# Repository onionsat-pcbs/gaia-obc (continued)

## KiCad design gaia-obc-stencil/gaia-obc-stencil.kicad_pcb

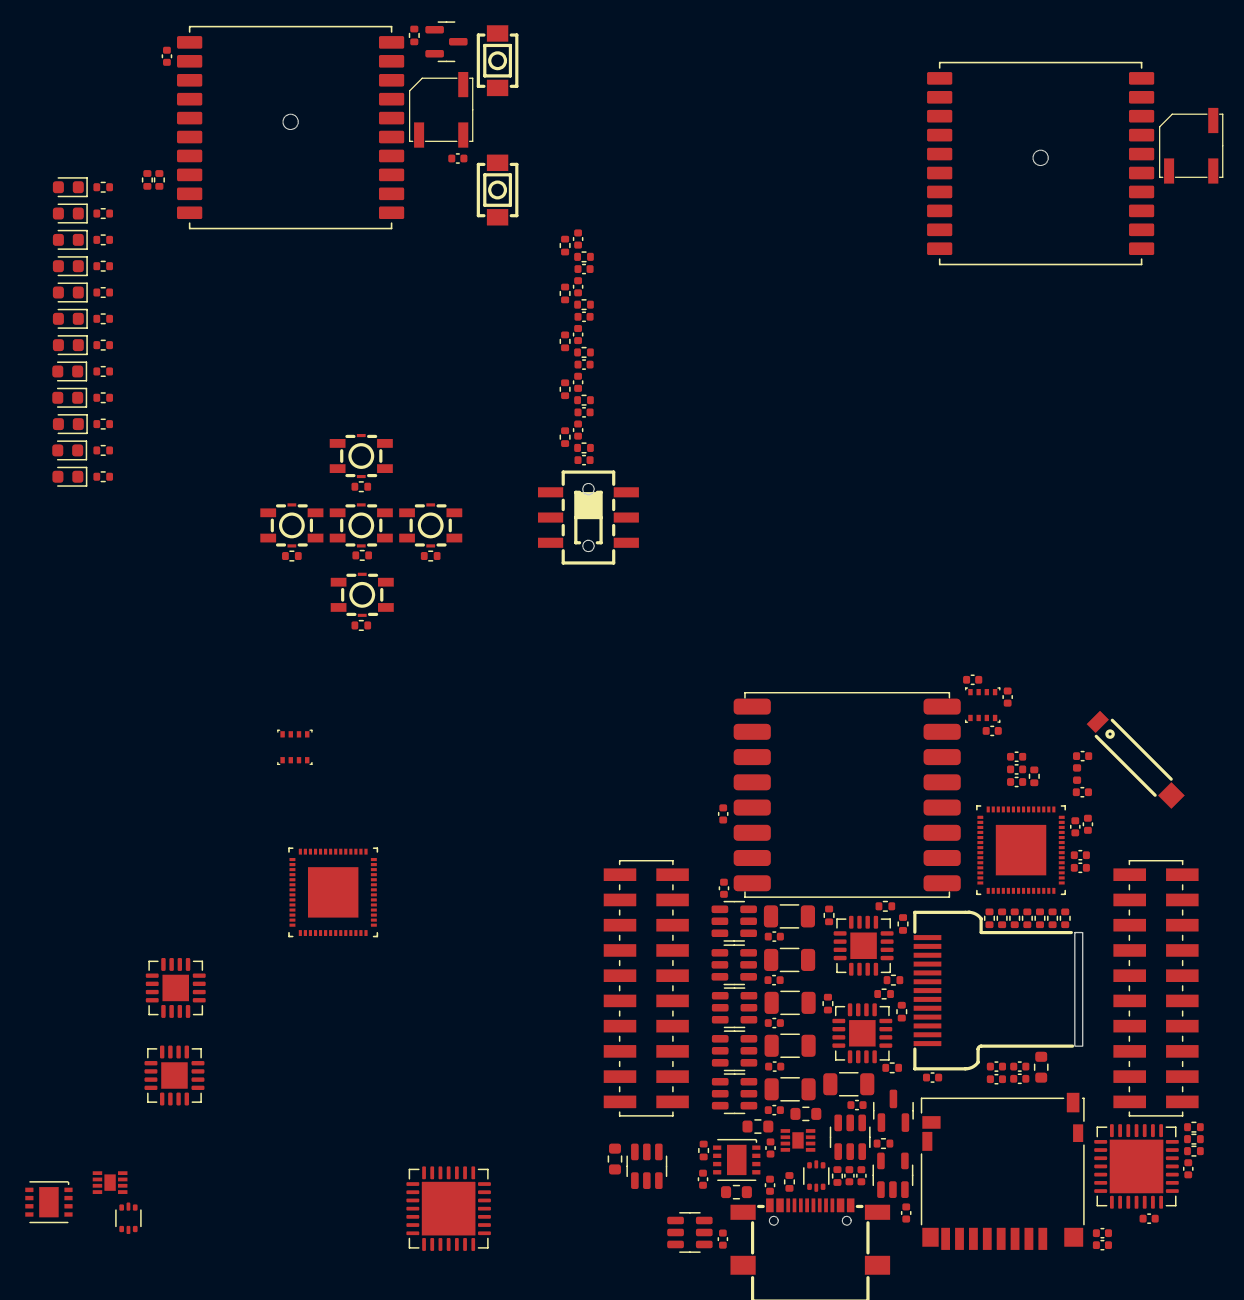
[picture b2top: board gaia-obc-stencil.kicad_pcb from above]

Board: 2 copper layers, 171 parts (1 on the bottom side), 121 nets, no tracks yet.

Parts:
AE1: Antenna; ANT-SMD_L8.0-W1.0
BZ1, BZ1#2: Buzzer; buzzer_MLT-5020
C1, C2, C3, C5, C8, C9, C10, C11, C12, C25, C32, C36, C39, C40, C41, C43, C44, C45, C48: 100nF; C_0402_1005Metric
C4, C33, C35, C37: 10uF; C_0402_1005Metric
C6, C7, C13, C14, C15, C16, C17, C18, C24, C26, C27, C28, C29, C30, C31, C34, C38, C42: 1uF; C_0402_1005Metric
C19, C20, C21, C22, C23: 1nF; C_0402_1005Metric
C46: 2,4pF; C_0402_1005Metric
C47: 2,0pF; C_0402_1005Metric
D1, D2, D3, D4, D5, D6, D7, D8, D9, D10, D11, D12: LED_Small; LED_0603_1608Metric
IC1, IC1#2: MAX17048G+T10; SON50P200X200X80-9N-D
J1: USB_C_Receptacle_USB2.0_16P; USB-SMD_TYPE-C-16PQT-073
J2, J3: Conn_02x10_Odd_Even; PinHeader_2x10_P2.00mm_Vertical_SMD
J5: Micro_SD_Card_Det2; microSD_HC_Hirose_DM3D-SF
L1: 2,4nH; L_0402_1005Metric
Q1: IRLML6244; SOT-23
Q2: FS8205A; SOT-23-6
Q3: BSS138; SOT-23
R1, R2, R3, R13, R14, R15, R16, R17, R18, R20, R23, R24, R25, R26, R27, R28, R29, R30, R31, R59, R61, R62, R63, R64, R65: 10k; R_0402_1005Metric
R4, R5: 5.1k; R_0402_1005Metric
R6, R7, R8, R9, R10, R11, R12, R21, R22, R49, R50: TBA; R_0402_1005Metric
R19, R53: 1k; R_0402_1005Metric
R32, R33, R34, R35, R36, R37: 0,1; R_1206_3216Metric
R38, R39, R40, R41, R42, R43, R44, R45, R46, R47: 0; R_0402_1005Metric
R48: 100; R_0603_1608Metric
R51: 1k; R_0603_1608Metric
R54, R55: 100k; R_0603_1608Metric
R56, R57: 470; R_0402_1005Metric
R58: R_Small; R_0402_1005Metric
R60: 10; R_0603_1608Metric
SW1, SW2: SW_Push; KEY-SMD_L4.0-W3.0-LS4.9-1
SW3, SW4, SW5, SW6, SW7: SW_Push; KEY-SMD_4P-L3.1-W3.1-P2.00-LS4.0
SW8: SW_Slide_DPDT; MS-22D28-G020
U1, U1#2: MCP23017_ML; QFN-28-1EP_6x6mm_P0.65mm_EP4.25x4.25mm
U2, U2#2: USBLC6-2P6; SOT-666
U3, U3#2: ESP32-S3-PICO-1-N8R2; PQFN40P700X700X106-57N
U4, U4#2, U5, U5#2: INA3221; Texas_RGV0016A_VQFN-16-1EP_4x4mm_P0.65mm_EP2.1x2.1mm
U6, U7, U8, U9, U10: TPS22917DBV; SOT-23-6
U11: AP2112K-3.3; SOT-23-6
U12: DW01A; SOT-23-6
U13: AP2112K-3.0; SOT-23-5
U14, U14#2: LGS4056HDB; DFN-8-1EP_3x3mm_P0.65mm_EP1.55x2.4mm
U15, U15#2: CD-PA1616; XCVR_CD-PA1616D
U16: RFM95W-868S2; HOPERF_RFM9XW_SMD
U17, U17#2: BME280; Bosch_LGA-8_2.5x2.5mm_P0.65mm_ClockwisePinNumbering
U18: OLED-SMD_ST7735S

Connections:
+3.3V: BZ1.1 (+), BZ1#2.1 (+), C1.2, C2.1, C7.1, C8.1, C9.1, C10.1, C11.1, C12.1, C13.1, C25.1, C26.2, C39.1, C40.2, C41.2, C42.2, C43.1, C44.1, C45.2, C48.2, J5.4 (VDD), R1.1, R2.1, R3.1, R13.1, R14.2, R15.2, R16.2, R17.2, R18.2, R20.2, R23.2, R24.1, R25.1, R26.1, R27.1, R28.1, R29.1, SW3.2, SW4.2, SW5.2, SW6.2, SW7.2, U1.5 (VDD), U1#2.5 (VDD), U3.2 (VDD3P3), U3.3 (VDD3P3), U3.20 (VDD3P3_RTC), U3.46 (VDD3P3_CPU), U3.55 (VDDA), U3.56 (VDDA), U3#2.2 (VDD3P3), U3#2.3 (VDD3P3), U3#2.20 (VDD3P3_RTC), U3#2.46 (VDD3P3_CPU), U3#2.55 (VDDA), U3#2.56 (VDDA), U4.4 (VS), U4#2.4 (VS), U5.4 (VS), U5.5 (A0), U5#2.4 (VS), U5#2.5 (A0), U11.5 (VOUT), U15.1 (VCC), U15#2.1 (VCC), U16.13 (3.3V), U17.2 (CSB), U17.6 (VDDIO), U17.8 (VDD), U17#2.2 (CSB), U17#2.6 (VDDIO), U17#2.8 (VDD)
+3V0: C36.1, C38.2, R59.1, U13.5 (VOUT), U18.10 (VCC), U18.12 (LEDA)
+BATT: C33.2, C37.2, IC1.2 (CELL), IC1.3 (VDD), IC1#2.2 (CELL), IC1#2.3 (VDD), J3.17, J3.18, R48.1, R55.2, SW8.1 (A), SW8.6 (C), U14.5 (BAT), U14#2.5 (BAT)
-BATT: J3.19, J3.20, Q2.3, R51.1
/EN_A1: U1.17 (GPA0), U1#2.17 (GPA0), U6.3 (ON)
/EN_A2: U1.18 (GPA1), U1#2.18 (GPA1), U7.3 (ON)
/EN_A3: U1.19 (GPA2), U1#2.19 (GPA2), U8.3 (ON)
/EN_B1: U1.20 (GPA3), U1#2.20 (GPA3), U9.3 (ON)
/EN_B2: U1.21 (GPA4), U1#2.21 (GPA4), U10.3 (ON)
/EXP0_USART_RXD: J2.14, U3.41 (GPIO36), U3#2.41 (GPIO36)
/EXP0_USART_TXD: J2.12, U3.42 (GPIO37), U3#2.42 (GPIO37)
/EXP1_SPI_CS: J2.5, U3.43 (GPIO38), U3#2.43 (GPIO38)
/EXP2_USART_RXD: J2.13, U3.39 (GPIO34), U3#2.39 (GPIO34)
/EXP2_USART_TXD: J2.11, U3.40 (GPIO35), U3#2.40 (GPIO35)
/GPS_RX: R57.2, U3.6 (GPIO1), U3#2.6 (GPIO1)
/GPS_TX: R56.1, U3.7 (GPIO2), U3#2.7 (GPIO2)
/LORA_CS: U3.27 (GPIO21), U3#2.27 (GPIO21), U16.5 (NSS)
/LORA_RESET: U3.38 (GPIO33), U3#2.38 (GPIO33), U16.6 (RESET)
/PB1: R61.2, SW3.1, U1.25 (GPB0), U1#2.25 (GPB0)
/PB2: R62.2, SW4.1, U1.26 (GPB1), U1#2.26 (GPB1)
/PB3: R63.2, SW5.1, U1.27 (GPB2), U1#2.27 (GPB2)
/PB4: R64.2, SW6.1, U1.28 (GPB3), U1#2.28 (GPB3)
/PB5: R65.2, SW7.1, U1.1 (GPB4), U1#2.1 (GPB4)
/Power Supply Unit/OBC_BATT: C24.1, C34.1, R37.2, U5.2 (IN+3), U5#2.2 (IN+3), U11.1 (VIN), U11.3 (EN), U13.1 (VIN), U13.3 (EN)
/SCREEN_CLK: U3.11 (GPIO6), U3#2.11 (GPIO6), U18.4 (SCL)
/SCREEN_CS: U3.8 (GPIO3), U3#2.8 (GPIO3), U18.7 (CS)
/SCREEN_DC: U3.10 (GPIO5), U3#2.10 (GPIO5), U18.5 (RS)
/SCREEN_MOSI: U3.12 (GPIO7), U3#2.12 (GPIO7), U18.3 (SDA)
/SCREEN_RESET: U3.9 (GPIO4), U3#2.9 (GPIO4), U18.6 (RES)
/SD_CS: J5.2 (DAT3/CD), U3.23 (GPIO17), U3#2.23 (GPIO17)
/USB_D+: U2.4 (I/O2), U2#2.4 (I/O2), U3.26 (GPIO20), U3#2.26 (GPIO20)
/USB_D-: U2.6 (I/O1), U2#2.6 (I/O1), U3.25 (GPIO19), U3#2.25 (GPIO19)
/VOUT_A1: C27.2, J3.1, J3.2, R38.2, R43.2, U6.6 (VOUT)
/VOUT_A2: C28.2, J3.3, J3.4, R39.2, R44.2, U7.6 (VOUT)
/VOUT_A3: C29.2, J3.5, J3.6, R40.2, R45.2, U8.6 (VOUT)
/VOUT_B1: C30.2, J3.7, J3.8, R41.2, R46.2, U9.6 (VOUT)
/VOUT_B2: C31.2, J3.9, J3.10, R42.2, R47.2, U10.6 (VOUT)
GND: C1.1, C2.2, C3.2, C4.1, C5.1, C6.2, C7.2, C8.2, C9.2, C10.2, C11.2, C12.2, C13.2, C14.1, C15.1, C16.1, C17.1, C18.1, C24.2, C25.2, C26.1, C27.1, C28.1, C29.1, C30.1, C31.1, C32.2, C33.1, C34.2, C35.1, C36.2, C37.1, C38.1, C39.2, C40.1, C41.1, C42.1, C43.2, C44.2, C45.1, C46.2, C47.1, C48.1, IC1.1 (CTG), IC1.4 (GND), IC1.9 (EP), IC1#2.1 (CTG), IC1#2.4 (GND), IC1#2.9 (EP), J1.A1B12 (GND), J1.B1A12 (GND), J1.S1 (SHIELD), J2.7, J2.9, J2.17, J2.18, J2.19, J2.20, J3.13, J3.14, J3.15, J3.16, J5.6 (VSS), J5.11 (SHIELD), Q1.2 (S), Q2.1, Q3.2 (S), R4.1, R5.2, R6.2, R7.2, R8.2, R9.2, R10.2, R11.2, R12.2, R21.2, R22.2, R43.1, R44.1, R45.1, R46.1, R47.1, R53.2, R54.1, R58.2, R61.1, R62.1, R63.1, R64.1, R65.1, SW1.1, SW2.1, U1.6 (VSS), U1.11 (A0), U1.12 (A1), U1.13 (A2), U1.29 (EP), U1#2.6 (VSS), U1#2.11 (A0), U1#2.12 (A1), U1#2.13 (A2), U1#2.29 (EP), U2.2 (GND), U2#2.2 (GND), U3.57 (GND), U3#2.57 (GND), U4.3 (GND), U4.5 (A0), U4.17 (EP), U4#2.3 (GND), U4#2.5 (A0), U4#2.17 (EP), U5.3 (GND), U5.17 (EP), U5#2.3 (GND), U5#2.17 (EP), U6.2 (GND), U7.2 (GND), U8.2 (GND), U9.2 (GND), U10.2 (GND), U11.2 (GND), U12.6 (GND), U13.2 (GND), U14.1 (TEMP), U14.3 (GND), U14.9 (EPAD), U14#2.1 (TEMP), U14#2.3 (GND), U14#2.9 (EPAD), U15.3 (GND), U15.8 (GND), U15.12 (GND), U15.19 (GND), U15#2.3 (GND), U15#2.8 (GND), U15#2.12 (GND), U15#2.19 (GND), U16.1 (GND), U16.8 (GND), U16.10 (GND), U17.1 (GND), U17.5 (SDO), U17.7 (GND), U17#2.1 (GND), U17#2.5 (SDO), U17#2.7 (GND), U18.8 (GND), U18.13 (GND)
I2C_1_SCL: IC1.7 (SCL), IC1#2.7 (SCL), J2.4, R15.1, U1.8 (SCK), U1#2.8 (SCK), U3.14 (GPIO9), U3#2.14 (GPIO9), U4.6 (SCL), U4#2.6 (SCL), U5.6 (SCL), U5#2.6 (SCL), U17.4 (SCK), U17#2.4 (SCK)
I2C_1_SDA: IC1.8 (SDA), IC1#2.8 (SDA), J2.2, R14.1, U1.9 (SDA), U1#2.9 (SDA), U3.13 (GPIO8), U3#2.13 (GPIO8), U4.7 (SDA), U4#2.7 (SDA), U5.7 (SDA), U5#2.7 (SDA), U17.3 (SDI), U17#2.3 (SDI)
I2C_2_SCL: J2.3, R20.1, U3.16 (GPIO11), U3#2.16 (GPIO11)
I2C_2_SDA: J2.1, R17.1, U3.15 (GPIO10), U3#2.15 (GPIO10)
unnamed: AE1.1 (A), C46.1, L1.1
unnamed: BZ1.2 (-), BZ1#2.2 (-), Q1.3 (D)
unnamed: D1.1 (K), R6.1
unnamed: D2.2 (A), U1.2 (GPB5), U1#2.2 (GPB5)
unnamed: D2.1 (K), R7.1
unnamed: D3.2 (A), U1.4 (GPB7), U1#2.4 (GPB7)
unnamed: D3.1 (K), R8.1
unnamed: D4.2 (A), U1.3 (GPB6), U1#2.3 (GPB6)
unnamed: D4.1 (K), R9.1
unnamed: D5.2 (A), U1.24 (GPA7), U1#2.24 (GPA7)
unnamed: D5.1 (K), R10.1
unnamed: D6.2 (A), U1.23 (GPA6), U1#2.23 (GPA6)
unnamed: D6.1 (K), R11.1
unnamed: D7.2 (A), U1.22 (GPA5), U1#2.22 (GPA5)
unnamed: D7.1 (K), R12.1
unnamed: D8.2 (A), U3.51 (GPIO45), U3#2.51 (GPIO45)
unnamed: D8.1 (K), R21.1
unnamed: D9.2 (A), U3.52 (GPIO46), U3#2.52 (GPIO46)
unnamed: D9.1 (K), R22.1
unnamed: D10.2 (A), U14.7 (~CHRG), U14#2.7 (~CHRG)
unnamed: D10.1 (K), R49.1
unnamed: D11.2 (A), U14.6 (~STDBY), U14#2.6 (~STDBY)
unnamed: D11.1 (K), R50.2
unnamed: D12.2 (A), U15.5 (3D-FIX), U15#2.5 (3D-FIX)
unnamed: D12.1 (K), R58.1
unnamed: IC1.6 (QSTRT), IC1#2.6 (QSTRT), R54.2
unnamed: IC1.5 (~ALRT), IC1#2.5 (~ALRT), R55.1
unnamed: J1.A5 (CC1), R4.2
unnamed: J1.B5 (CC2), R5.1
unnamed: J1.A6 (D+), J1.B6 (D+), U2.3 (I/O2), U2#2.3 (I/O2)
unnamed: J1.A7 (D-), J1.B7 (D-), U2.1 (I/O1), U2#2.1 (I/O1)
unnamed: Q1.1 (G), R19.2
unnamed: Q3.3 (D), R60.1
unnamed: Q3.1 (G), R59.2
unnamed: R2.2, U1.16 (INTA), U1#2.16 (INTA)
unnamed: R1.2, U1.15 (INTB), U1#2.15 (INTB)
unnamed: R3.2, U1.14 (~RESET), U1#2.14 (~RESET)
unnamed: C5.2, C6.1, R13.2, SW1.2, U3.4 (CHIP_PU), U3#2.4 (CHIP_PU)
unnamed: SW2.2, U3.5 (GPIO0), U3#2.5 (GPIO0)
unnamed: R19.1, U3.24 (GPIO18), U3#2.24 (GPIO18)
unnamed: C47.2, L1.2, U3.1 (LNA_IN), U3#2.1 (LNA_IN)
unnamed: R28.2, U4.9 (CRITICAL), U4#2.9 (CRITICAL)
unnamed: C14.2, C19.1, R32.2, U4.12 (IN+1), U4#2.12 (IN+1), U6.1 (VIN)
unnamed: C15.2, C20.1, R33.2, U4.15 (IN+2), U4#2.15 (IN+2), U7.1 (VIN)
unnamed: C16.2, C21.1, R34.2, U4.2 (IN+3), U4#2.2 (IN+3), U8.1 (VIN)
unnamed: R30.2, U4.10 (PV), U4#2.10 (PV)
unnamed: R24.2, U4.13 (TC), U4#2.13 (TC)
unnamed: R30.1, U4.16 (VPU), U4#2.16 (VPU)
unnamed: R26.2, U4.8 (WARNING), U4#2.8 (WARNING)
unnamed: R29.2, U5.9 (CRITICAL), U5#2.9 (CRITICAL)
unnamed: C17.2, C22.1, R35.2, U5.12 (IN+1), U5#2.12 (IN+1), U9.1 (VIN)
unnamed: R31.2, U5.10 (PV), U5#2.10 (PV)
unnamed: R25.2, U5.13 (TC), U5#2.13 (TC)
unnamed: R31.1, U5.16 (VPU), U5#2.16 (VPU)
unnamed: R27.2, U5.8 (WARNING), U5#2.8 (WARNING)
unnamed: C19.2, U6.4 (CT)
unnamed: R38.1, U6.5 (QOD)
unnamed: C20.2, U7.4 (CT)
unnamed: R39.1, U7.5 (QOD)
unnamed: C21.2, U8.4 (CT)
unnamed: R40.1, U8.5 (QOD)
unnamed: C22.2, U9.4 (CT)
unnamed: R41.1, U9.5 (QOD)
unnamed: C23.2, U10.4 (CT)
unnamed: R42.1, U10.5 (QOD)
unnamed: C18.2, C23.1, R36.2, U5.15 (IN+2), U5#2.15 (IN+2), U10.1 (VIN)
unnamed: R51.2, U12.2 (CS)
unnamed: Q2.4, U12.3 (OC)
unnamed: Q2.6, U12.1 (OD)
unnamed: C32.1, R48.2, U12.5 (VCC)
unnamed: R53.1, U14.2 (PROG), U14#2.2 (PROG)
unnamed: R57.1, U15.10 (RX), U15#2.10 (RX)
unnamed: R56.2, U15.9 (TX), U15#2.9 (TX)
unnamed: R60.2, U18.11 (LEDK)
SPI_0_MISO: J2.6, J5.7 (DAT0), R16.1, U3.17 (GPIO12), U3#2.17 (GPIO12), U16.2 (MISO)
SPI_0_MOSI: J2.8, J5.3 (CMD), R18.1, U3.18 (GPIO13), U3#2.18 (GPIO13), U16.3 (MOSI)
SPI_0_SCLK: J2.10, J5.5 (CLK), R23.1, U3.19 (GPIO14), U3#2.19 (GPIO14), U16.4 (SCK)
VBUS: C3.1, C4.2, C35.2, D1.2 (A), J1.A4B9 (VBUS), J1.B4A9 (VBUS), R49.2, R50.1, U2.5 (VBUS), U2#2.5 (VBUS), U14.4 (V_{CC}), U14.8 (CE), U14#2.4 (V_{CC}), U14#2.8 (CE)
VCC: R32.1, R33.1, R34.1, R35.1, R36.1, R37.1, SW8.2 (B), SW8.5 (B), U4.1 (IN-3), U4.11 (IN-1), U4.14 (IN-2), U4#2.1 (IN-3), U4#2.11 (IN-1), U4#2.14 (IN-2), U5.1 (IN-3), U5.11 (IN-1), U5.14 (IN-2), U5#2.1 (IN-3), U5#2.11 (IN-1), U5#2.14 (IN-2)

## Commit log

2025-05-28 initial release
2025-06-02 creating different sheets
2025-06-02 preparing ina3221
2025-06-03 creating psu switches
2025-06-03 finishing psu
2025-06-25 borad outline
2025-07-17 screen component added
2025-07-22 almost final release
2025-07-28 +buzzer component
2025-08-01 prep for routing 2/1
2025-08-03 almost routeable//98% done schema
2025-08-04 start routing
2025-08-05 Keepout(slidein place) added to User.4 layer
2025-08-05 ready for approval
2025-08-07 change screen
2025-08-09 Finalizing schematic+Start placing components
2025-08-10 finish placing components+small fixes in schema
2025-08-17 ROUTING 1/3
2025-08-24 ROUTING DONE 08. 24.
2025-08-24 fixing minor bugs
2025-08-24 cleaning up footprints + fixing DRC
2025-08-25 finalizing everything + creating stencil + ORDER 08. 25.
2025-08-25 fixing stencil
2025-08-26 Cleaning up schematics
2025-08-26 fixing BME280 position schematic
2025-08-26 exporting schematic to PDF
2025-11-05 fixing bugs v1.1-pre1
2025-11-06 fixing ANT bug v1.1-pre2
2025-11-06 Revert "fixing ANT bug v1.1-pre2"
    This reverts commit 9e563c6fd1f1bf527dff48955dff4f9202e18023.
2025-11-06 fixing routing problems v1.1-pre3
2025-11-07 v1.1-pre4 - fixing capacitors, ANT connector, optimizing routes
2025-11-09 v1.1-final - production
2025-11-09 adding position star
2025-11-10 fixing infill stroke
2025-12-01 obc v1.2-pre1
2025-12-01 v1.2
2025-12-01 adding logos + generating production files
2025-12-12 v1.3
2025-12-12 neptune 1.3 production
2025-12-28 v1.4 - adding interrupt for lora
2025-12-30 BGA pad size fix v1.4.1
2026-02-01 obc v1.5
2026-02-01 Fixing INA238 VBUS err
2026-02-01 v1.5 - PROD
